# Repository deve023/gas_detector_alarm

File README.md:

# Gas Detector Alarm

The system has a gas detector. When gas is detected a yellow LED turns on and an alarm buzzer rings. When gas is no longer present, the LED turns off but the sound alarm remains until the user presses the deactivation button. Cost: aproximately USD 16 if the components are purchased through Amazon.

# Block Diagram

The repository contains the VHD code describing the hardware, a test bench to try out the different scenarios and the circuit diagram. 3D design of the case is pending.

# Bill of Materials

# Case Example

In this scenario, pressing the button when the alarm is off does not change the output. Once gas is detected, LED and buzzer both turn on. If gas is no longer detected, LED goes off but buzzer remains. Only when pressing the button does the buzzer turn off. Furthermore, if gas is detected when the button is on, the user must release the button and press it again to deactivate the alarm. This last functionality is set like this in case the button gets stuck, if that is the case and the user is unaware of the button's condition the alarm would go off anyway.

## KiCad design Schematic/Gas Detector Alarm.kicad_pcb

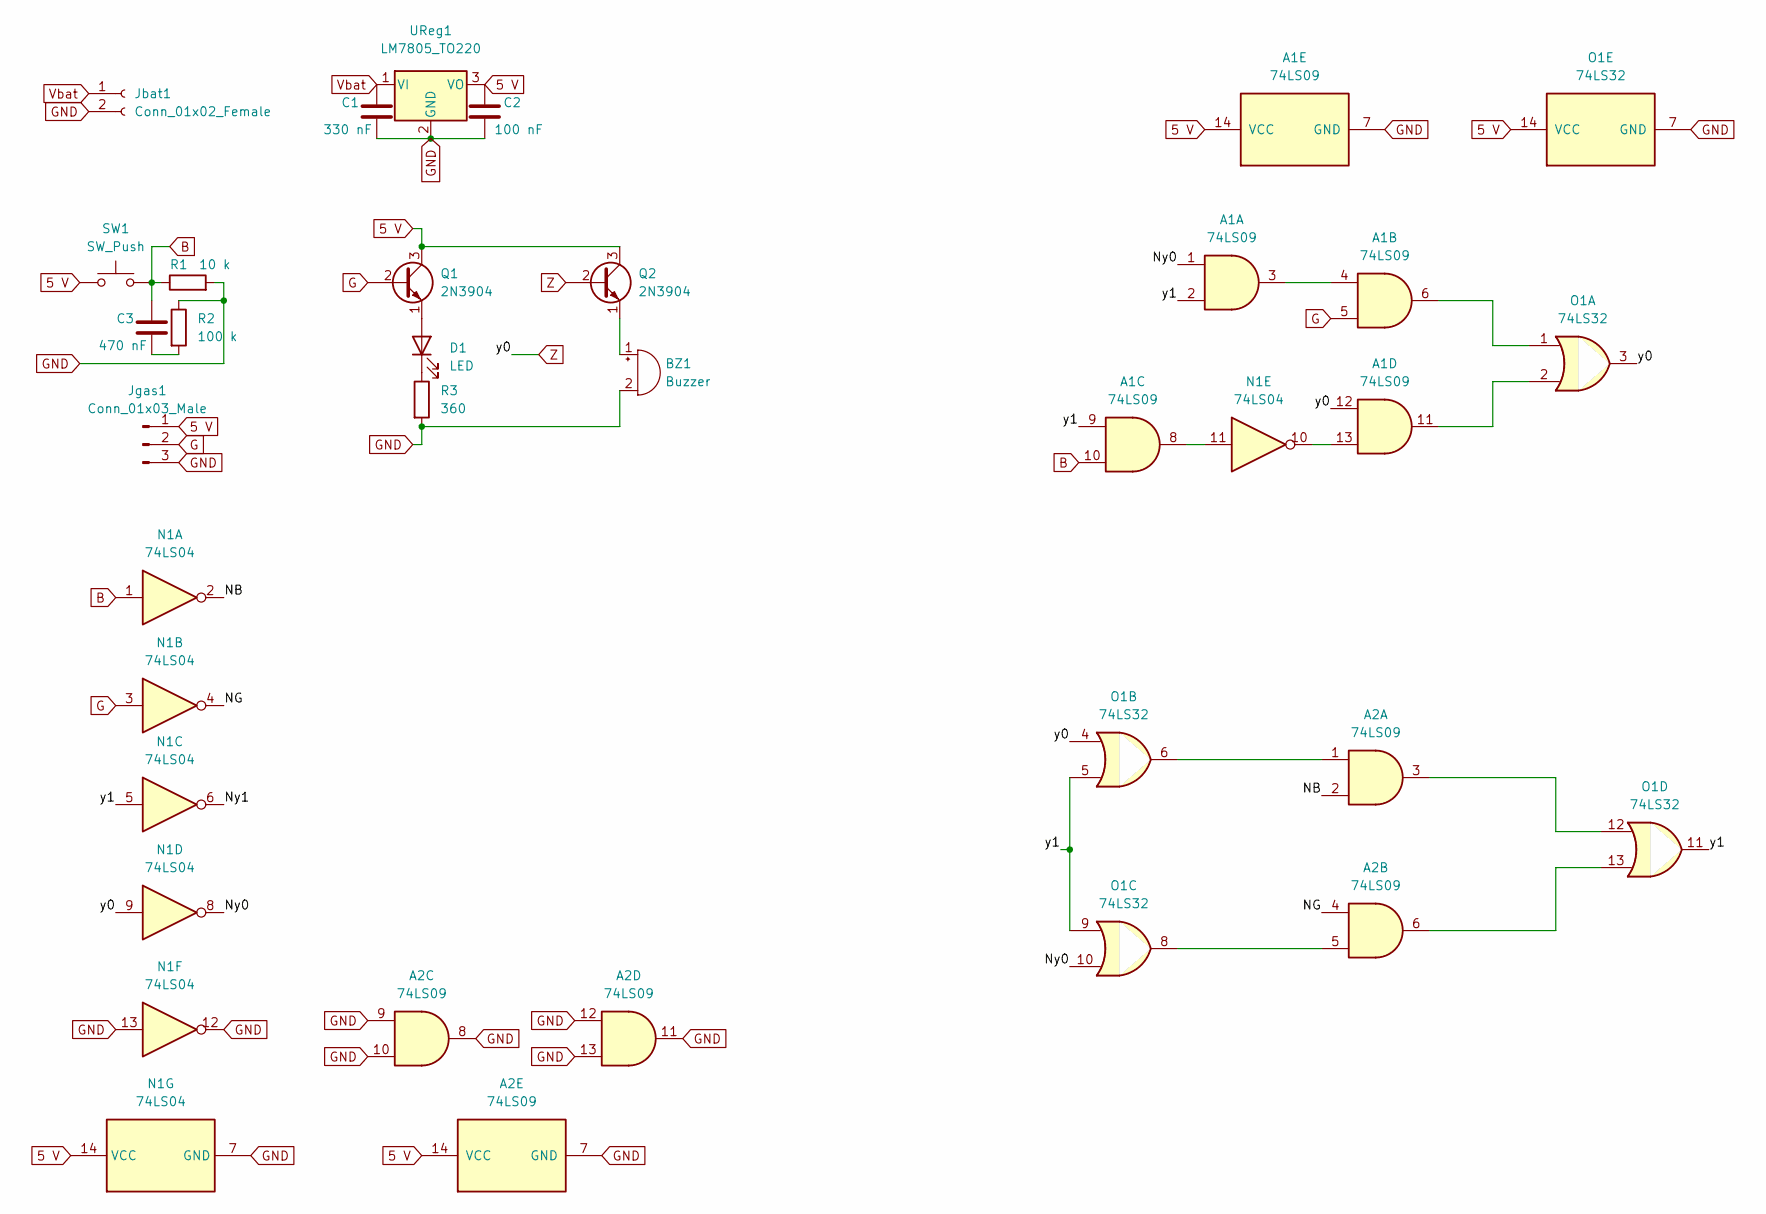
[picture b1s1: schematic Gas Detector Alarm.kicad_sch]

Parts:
A1, A2: 74LS09; DIP_Socket-14_W4.3_W5.08_W7.62_W10.16_W10.9_3M_214-3339-00-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
BZ1: Buzzer; Buzzer_15x7.5RM7.6
C1: 330 nF; C_Disc_D9.0mm_W5.0mm_P5.00mm
C2: 100 nF; C_Disc_D9.0mm_W5.0mm_P5.00mm
C3: 470 nF; C_Disc_D9.0mm_W5.0mm_P5.00mm
D1: LED; LED_D3.0mm
Jbat1: Conn_01x02_Female; PinSocket_1x02_P1.00mm_Vertical
Jgas1: Conn_01x03_Male; PinHeader_1x03_P1.00mm_Vertical
N1: 74LS04; DIP_Socket-14_W4.3_W5.08_W7.62_W10.16_W10.9_3M_214-3339-00-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
O1: 74LS32; DIP_Socket-14_W4.3_W5.08_W7.62_W10.16_W10.9_3M_214-3339-00-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
Q1, Q2: 2N3904; TO-92_Inline
R1: 10 k; R_Axial_DIN0207_L6.3mm_D2.5mm_P2.54mm_Vertical
R2: 100 k; R_Axial_DIN0207_L6.3mm_D2.5mm_P2.54mm_Vertical
R3: 360; R_Axial_DIN0207_L6.3mm_D2.5mm_P2.54mm_Vertical
SW1: SW_Push; SW_PUSH_6mm_H5mm
UReg1: LM7805_TO220; TO-220-3_Vertical

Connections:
5 V: A1.14 (VCC), A2.14 (VCC), C2.1, Jgas1.1, N1.14 (VCC), O1.14 (VCC), Q1.3 (C), Q2.3 (C), SW1.1, UReg1.3 (VO)
/NB: A2.2, N1.2
/NG: A2.4, N1.4
/Ny0: A1.1, N1.8, O1.10
/Ny1: N1.6
/y1: A1.2, A1.9, N1.5, O1.5, O1.9, O1.11
B: A1.10, C3.1, N1.1, R1.1, SW1.2
G: A1.5, Jgas1.2, N1.3, Q1.2 (B)
GND: A1.7 (GND), A2.7 (GND), A2.8, A2.9, A2.10, A2.11, A2.12, A2.13, BZ1.2 (+), C1.2, C2.2, Jbat1.2, Jgas1.3, N1.7 (GND), N1.12, N1.13, O1.7 (GND), R1.2, R2.1, R3.2, UReg1.2 (GND)
unnamed: A1.3, A1.4
unnamed: A1.6, O1.1
unnamed: A1.11, O1.2
unnamed: A2.1, O1.6
unnamed: A2.6, O1.13
unnamed: C3.2, R2.2
unnamed: D1.1 (K), R3.1
unnamed: D1.2 (A), Q1.1 (E)
unnamed: A1.13, N1.10
unnamed: A1.8, N1.11
unnamed: A2.5, O1.8
unnamed: A2.3, O1.12
unnamed: BZ1.1 (-), Q2.1 (E)
Vbat: C1.1, Jbat1.1, UReg1.1 (VI)
Z: A1.12, N1.9, O1.3, O1.4, Q2.2 (B)

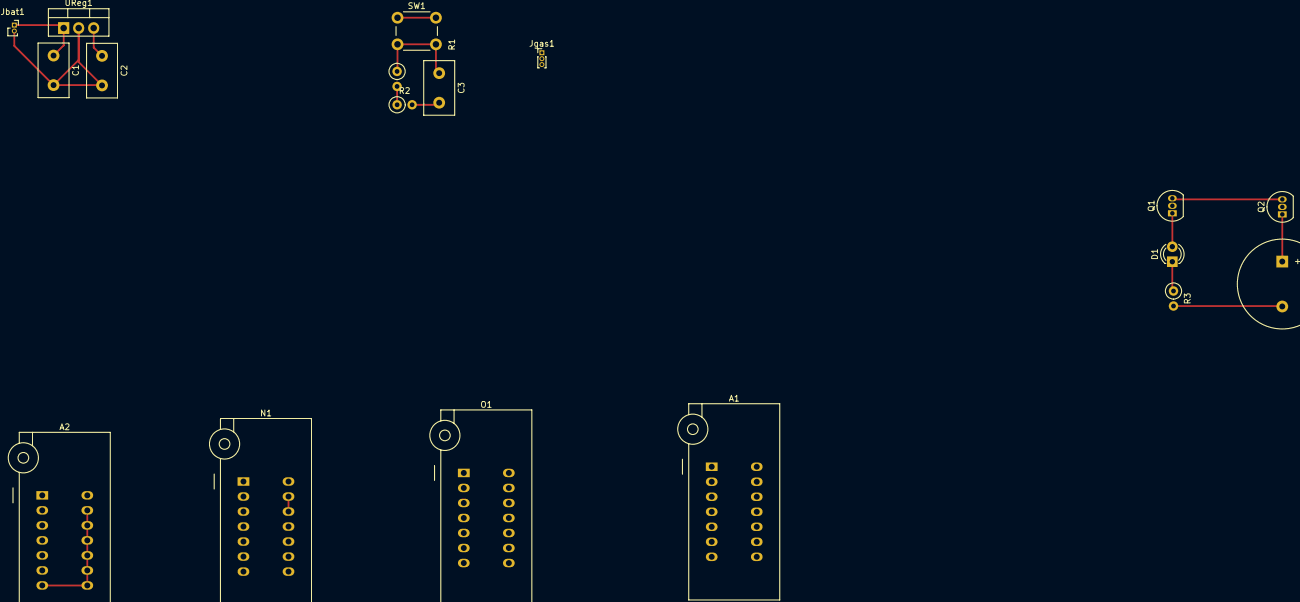
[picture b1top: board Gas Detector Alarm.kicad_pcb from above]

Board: 2 copper layers, 18 parts (0 on the bottom side), 23 nets.

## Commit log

2023-11-24 Main VHD files
2023-11-24 Schematic upload
2023-11-24 Added output example to the readme
2023-11-24 README minor update
2023-11-24 Update README.md (added functionality)
2023-11-24 Fixed functionality of release and press button to turn off present alarm.
2023-11-24 Test bench of added functionality
2023-11-24 VHD code improvement
2023-11-24 Reorganizing VHD file structure in \src
2023-11-24 Reorganizing VHD files in \src
2023-11-24 Schematic v2
2023-11-24 Add PCB schematic file v1 (In progress)
2023-11-24 Schematic v2 in PDF for easier visualization
